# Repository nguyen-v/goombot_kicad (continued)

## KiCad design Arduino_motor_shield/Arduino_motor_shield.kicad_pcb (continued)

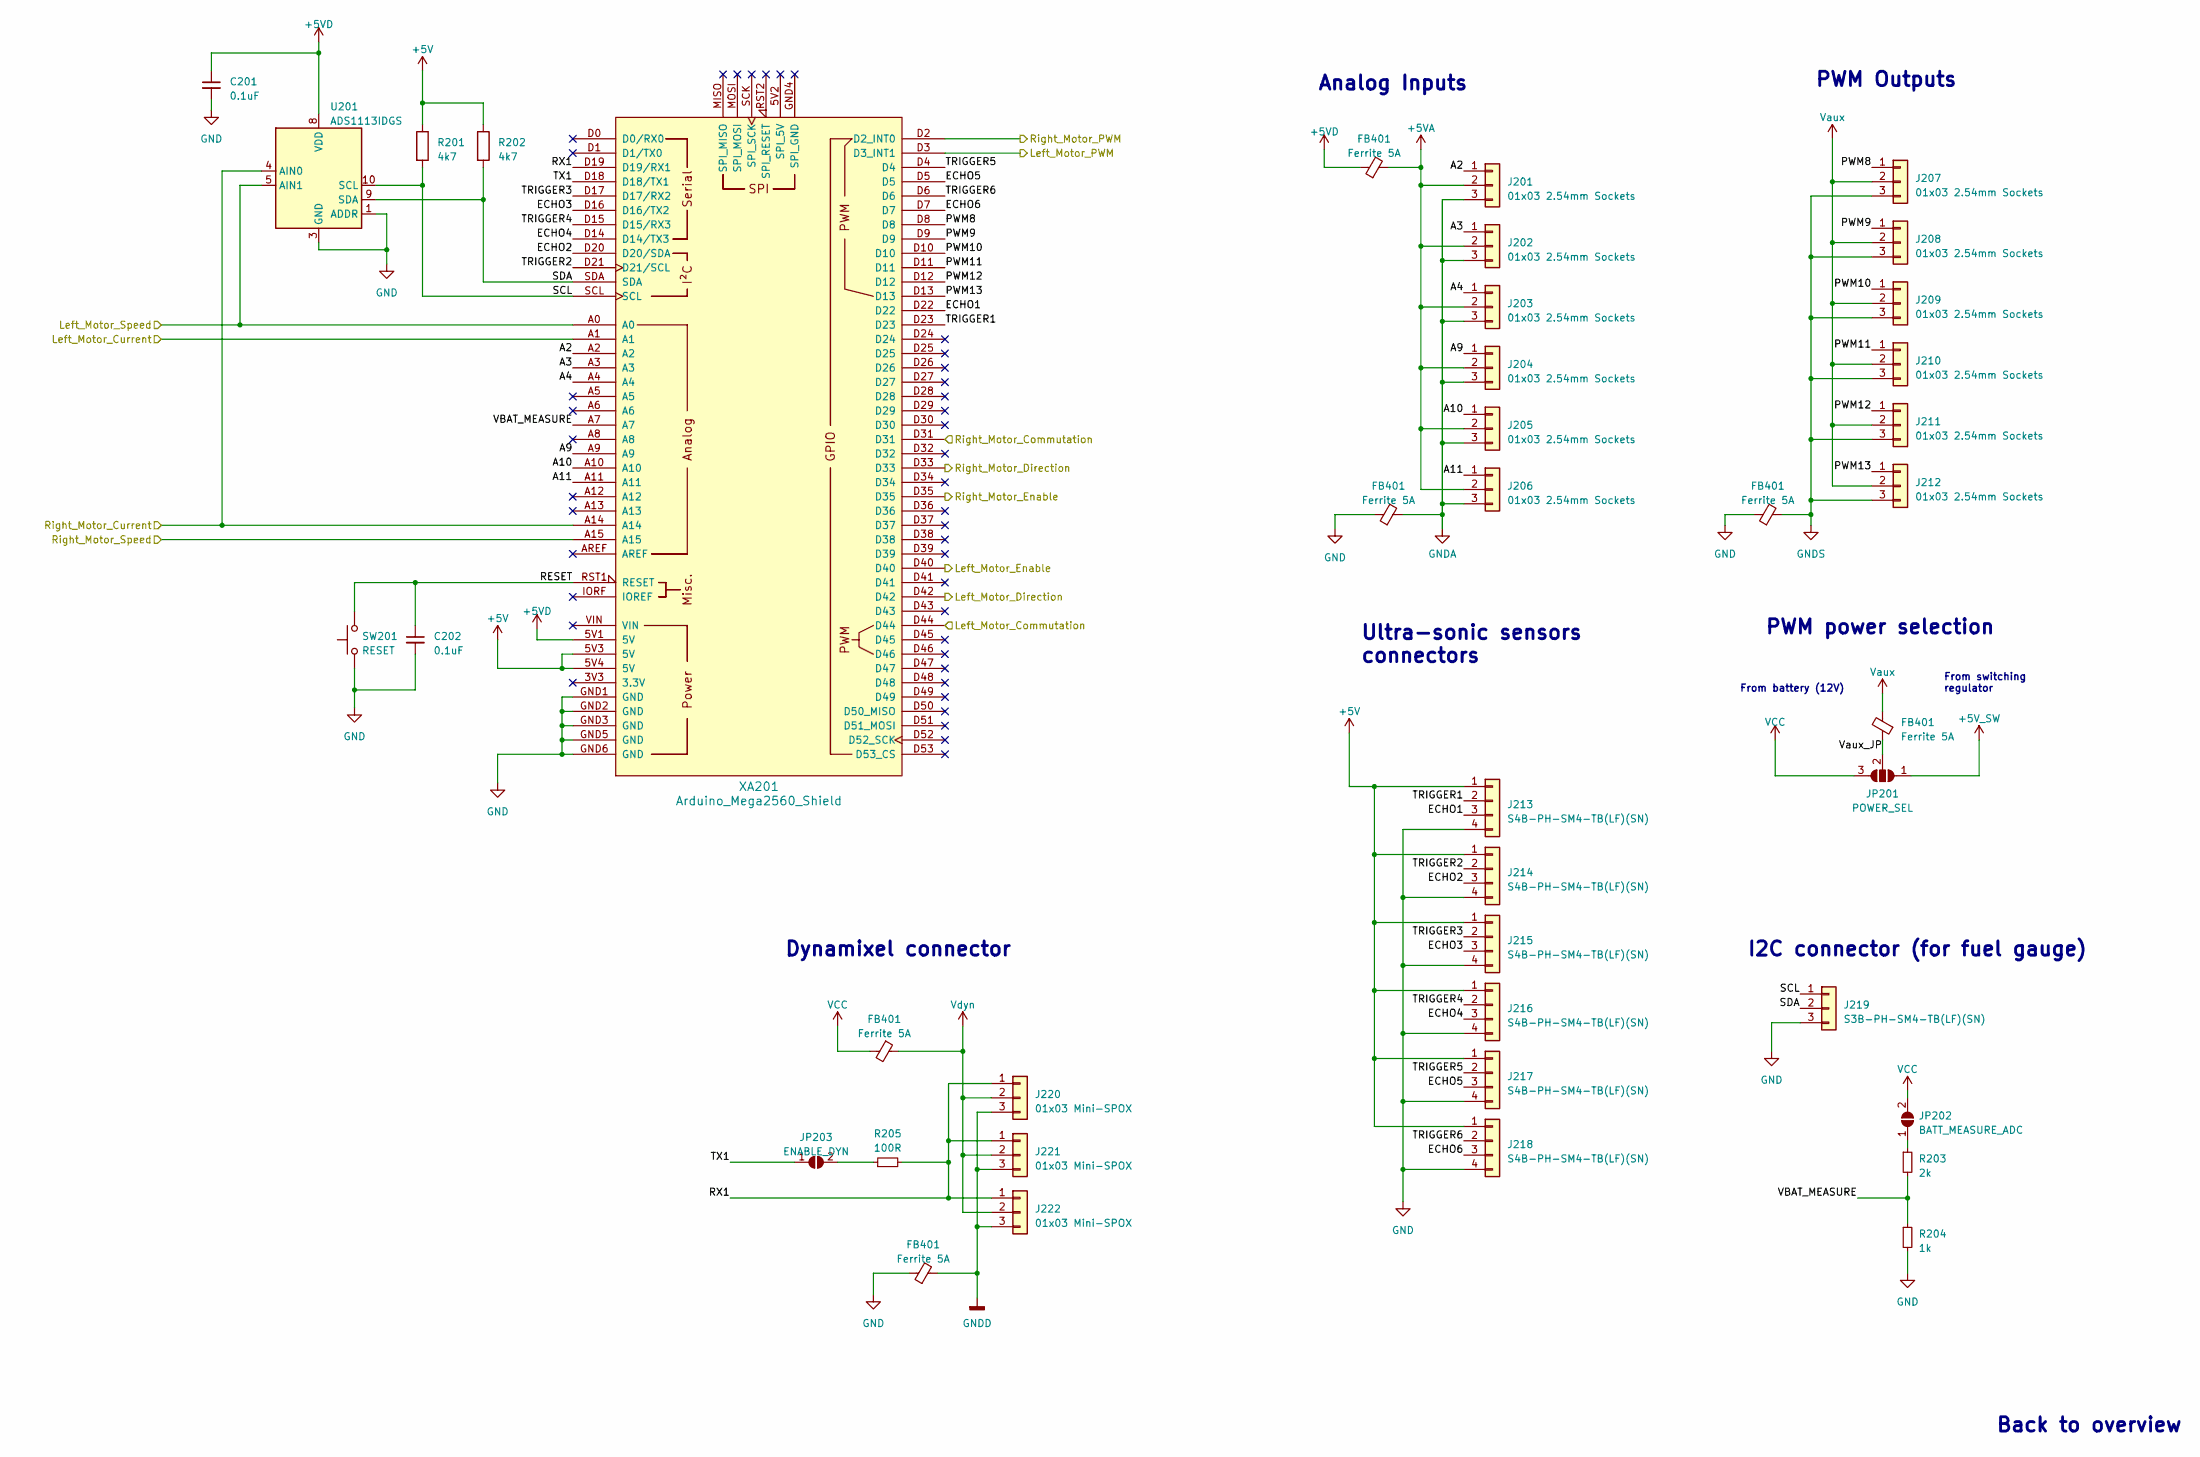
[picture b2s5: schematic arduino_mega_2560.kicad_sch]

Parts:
C201, C202: 0.1uF; C_0603_1608Metric
FB401: Ferrite 5A; L_0603_1608Metric
J201, J202, J203, J204, J205, J206, J207, J208, J209, J210, J211, J212: 01x03 2.54mm Sockets; PinSocket_1x03_P2.54mm_Vertical
J213, J214, J215, J216, J217, J218: S4B-PH-SM4-TB(LF)(SN); JST_PH_S4B-PH-SM4-TB_1x04-1MP_P2.00mm_Horizontal
J219: S3B-PH-SM4-TB(LF)(SN); JST_PH_S3B-PH-SM4-TB_1x03-1MP_P2.00mm_Horizontal
J220, J221, J222: 01x03 Mini-SPOX; MOLEX_0022057035_5268-03A
JP201: POWER_SEL; SolderJumper-3_P1.3mm_Open_RoundedPad1.0x1.5mm
JP202: BATT_MEASURE_ADC; SolderJumper-2_P1.3mm_Open_RoundedPad1.0x1.5mm
JP203: ENABLE_DYN; SolderJumper-2_P1.3mm_Open_RoundedPad1.0x1.5mm
R201, R202: 4k7; R_0603_1608Metric
R203: 2k; R_0603_1608Metric
R204: 1k; R_0603_1608Metric
R205: 100R; R_0603_1608Metric
SW201: RESET; MJTP1140ATR
U201: ADS1113IDGS; TSSOP-10_3x3mm_P0.5mm
XA201: Arduino_Mega2560_Shield

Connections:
+5V: J213.1, J214.1, J215.1, J216.1, J217.1, J218.1, R201.1, R202.1, XA201.5V3 (5V), XA201.5V4 (5V)
+5VA: J201.2, J202.2, J203.2, J204.2, J205.2, J206.2; also elsewhere on the board
+5VD: C201.1, U201.8 (VDD), XA201.5V1 (5V); also elsewhere on the board
/Arduino Mega 2560/A2: J201.1, XA201.A2
/Arduino Mega 2560/A3: J202.1, XA201.A3
/Arduino Mega 2560/A4: J203.1, XA201.A4
/Arduino Mega 2560/A9: J204.1, XA201.A9
/Arduino Mega 2560/A10: J205.1, XA201.A10
/Arduino Mega 2560/A11: J206.1, XA201.A11
/Arduino Mega 2560/ECHO1: J213.3, XA201.D22
/Arduino Mega 2560/ECHO2: J214.3, XA201.D20 (D20/SDA)
/Arduino Mega 2560/ECHO3: J215.3, XA201.D16 (D16/TX2)
/Arduino Mega 2560/ECHO4: J216.3, XA201.D14 (D14/TX3)
/Arduino Mega 2560/ECHO5: J217.3, XA201.D5
/Arduino Mega 2560/ECHO6: J218.3, XA201.D7
/Arduino Mega 2560/Left_Motor_Commutation: XA201.D44; also elsewhere on the board
/Arduino Mega 2560/Left_Motor_Current: XA201.A1; also elsewhere on the board
/Arduino Mega 2560/Left_Motor_Direction: XA201.D42; also elsewhere on the board
/Arduino Mega 2560/Left_Motor_Enable: XA201.D40; also elsewhere on the board
/Arduino Mega 2560/Left_Motor_PWM: XA201.D3 (D3_INT1); also elsewhere on the board
/Arduino Mega 2560/Left_Motor_Speed: U201.5 (AIN1), XA201.A0; also elsewhere on the board
/Arduino Mega 2560/PWM8: J207.1, XA201.D8
/Arduino Mega 2560/PWM9: J208.1, XA201.D9
/Arduino Mega 2560/PWM10: J209.1, XA201.D10
/Arduino Mega 2560/PWM11: J210.1, XA201.D11
/Arduino Mega 2560/PWM12: J211.1, XA201.D12
/Arduino Mega 2560/PWM13: J212.1, XA201.D13
/Arduino Mega 2560/RESET: C202.1, SW201.2, XA201.RST1 (RESET)
/Arduino Mega 2560/RX1: J220.1, J221.1, J222.1, R205.2, XA201.D19 (D19/RX1)
/Arduino Mega 2560/Right_Motor_Commutation: XA201.D31; also elsewhere on the board
/Arduino Mega 2560/Right_Motor_Current: U201.4 (AIN0), XA201.A14; also elsewhere on the board
/Arduino Mega 2560/Right_Motor_Direction: XA201.D33; also elsewhere on the board
/Arduino Mega 2560/Right_Motor_Enable: XA201.D35; also elsewhere on the board
/Arduino Mega 2560/Right_Motor_PWM: XA201.D2 (D2_INT0); also elsewhere on the board
/Arduino Mega 2560/Right_Motor_Speed: XA201.A15; also elsewhere on the board
/Arduino Mega 2560/SCL: J219.1, R201.2, U201.10 (SCL), XA201.SCL
/Arduino Mega 2560/SDA: J219.2, R202.2, U201.9 (SDA), XA201.SDA
/Arduino Mega 2560/TRIGGER1: J213.2, XA201.D23
/Arduino Mega 2560/TRIGGER2: J214.2, XA201.D21 (D21/SCL)
/Arduino Mega 2560/TRIGGER3: J215.2, XA201.D17 (D17/RX2)
/Arduino Mega 2560/TRIGGER4: J216.2, XA201.D15 (D15/RX3)
/Arduino Mega 2560/TRIGGER5: J217.2, XA201.D4
/Arduino Mega 2560/TRIGGER6: J218.2, XA201.D6
/Arduino Mega 2560/TX1: JP203.1 (A), XA201.D18 (D18/TX1)
/Arduino Mega 2560/Vaux_JP: JP201.2 (C); also elsewhere on the board
GNDA: J201.3, J202.3, J203.3, J204.3, J205.3, J206.3; also elsewhere on the board
GNDD: J220.3, J221.3, J222.3; also elsewhere on the board
GNDS: J207.3, J208.3, J209.3, J210.3, J211.3, J212.3; also elsewhere on the board
unnamed: JP202.1 (A), R203.1
unnamed: JP203.2 (B), R205.1
VCC: JP201.3 (B), JP202.2 (B); also elsewhere on the board
Vaux: J207.2, J208.2, J209.2, J210.2, J211.2, J212.2; also elsewhere on the board
Vdyn: J220.2, J221.2, J222.2; also elsewhere on the board

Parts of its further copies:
FB201, FB202, FB203, FB204, FB205, FB206: Ferrite 5A; L_0603_1608Metric

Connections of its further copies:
+5VA: FB202.2; also elsewhere on the board
+5VD: FB202.1; also elsewhere on the board
/Arduino Mega 2560/Vaux_JP: FB204.1; also elsewhere on the board
GNDA: FB201.2; also elsewhere on the board
GNDD: FB206.2; also elsewhere on the board
GNDS: FB203.2; also elsewhere on the board
VCC: FB205.2; also elsewhere on the board
Vaux: FB204.2; also elsewhere on the board
Vdyn: FB205.1; also elsewhere on the board

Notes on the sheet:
From switching regulator
From battery (12V)
PWM Outputs
Analog Inputs
Dynamixel connector
I2C connector (for fuel gauge)
PWM power selection
Back to overview
Ultra-sonic sensors connectors

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
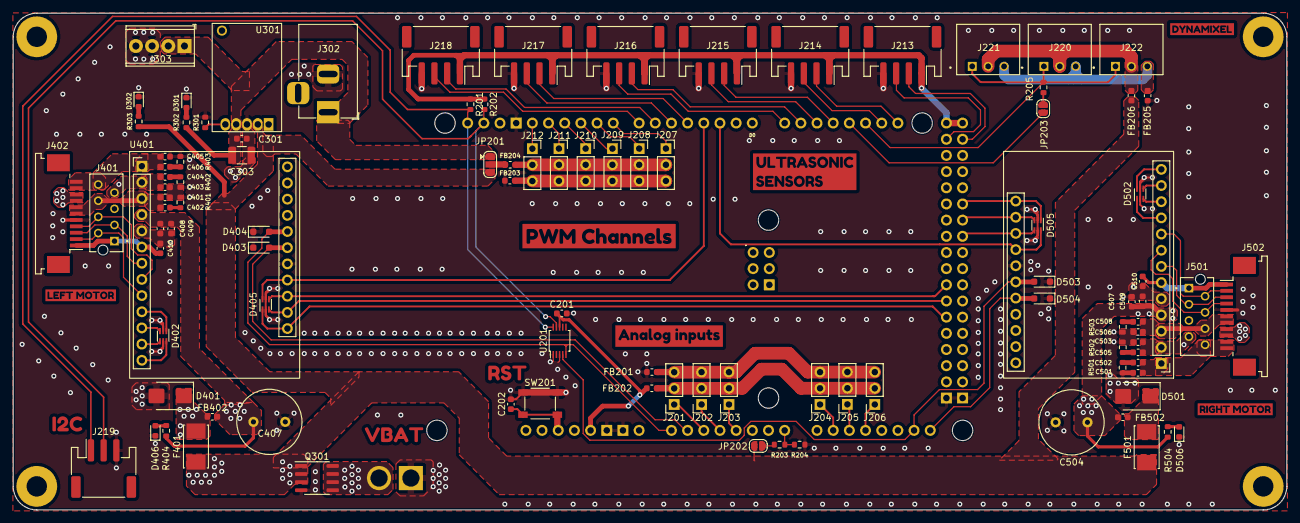
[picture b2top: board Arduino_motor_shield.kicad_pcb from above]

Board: 2 copper layers, 200.0 x 78.0 mm, 149 parts (1 on the bottom side), 94 nets.

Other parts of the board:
kibuzzard-6436BD05: G***; kibuzzard-6436BD05
kibuzzard-6436BD85: G***; kibuzzard-6436BD85
kibuzzard-6436BDA4: G***; kibuzzard-6436BDA4
kibuzzard-6436BDB6: G***; kibuzzard-6436BDB6
kibuzzard-6436BE0F: G***; kibuzzard-6436BE0F
kibuzzard-6436BE25: G***; kibuzzard-6436BE25
kibuzzard-6436BE36: G***; kibuzzard-6436BE36
kibuzzard-6436BEC4: G***; kibuzzard-6436BEC4
kibuzzard-6436BECD: G***; kibuzzard-6436BECD
kibuzzard-6436BED4: G***; kibuzzard-6436BED4
kibuzzard-6436BEDB: G***; kibuzzard-6436BEDB
kibuzzard-6436BEE8: G***; kibuzzard-6436BEE8
kibuzzard-6436BEF0: G***; kibuzzard-6436BEF0
kibuzzard-6436BF7A, kibuzzard-6436BF7A#2: G***; kibuzzard-6436BF7A
kibuzzard-6436BF9D, kibuzzard-6436BF9D#2, kibuzzard-6436BF9D#3, kibuzzard-6436BF9D#4: G***; kibuzzard-6436BF9D
kibuzzard-6436BF49: G***; kibuzzard-6436BF49
kibuzzard-6436BFC3: G***; kibuzzard-6436BFC3
kibuzzard-6436C0DF: G***; kibuzzard-6436C0DF
kibuzzard-6436C002: G***; kibuzzard-6436C002
kibuzzard-6436C2A5: G***; kibuzzard-6436C2A5
kibuzzard-6436C2D2: G***; kibuzzard-6436C2D2
kibuzzard-6436C3BB: G***; kibuzzard-6436C3BB
kibuzzard-6436C3CE: G***; kibuzzard-6436C3CE
kibuzzard-6436C4A8: G***; kibuzzard-6436C4A8
kibuzzard-6436C4AB: G***; kibuzzard-6436C4AB
kibuzzard-6436C4B8: G***; kibuzzard-6436C4B8
kibuzzard-6436C4F6: G***; kibuzzard-6436C4F6
kibuzzard-6436C26E: G***; kibuzzard-6436C26E
kibuzzard-6436C28D: G***; kibuzzard-6436C28D
kibuzzard-6436C31D, kibuzzard-6436C31D#2: G***; kibuzzard-6436C31D
kibuzzard-6436C50F: G***; kibuzzard-6436C50F
kibuzzard-6436C52E: G***; kibuzzard-6436C52E
kibuzzard-6436C224: G***; kibuzzard-6436C224
kibuzzard-6436C547: G***; kibuzzard-6436C547
kibuzzard-6436C551: G***; kibuzzard-6436C551
kibuzzard-6436C957: G***; kibuzzard-6436C957
kibuzzard-6436CBBB: G***; kibuzzard-6436CBBB

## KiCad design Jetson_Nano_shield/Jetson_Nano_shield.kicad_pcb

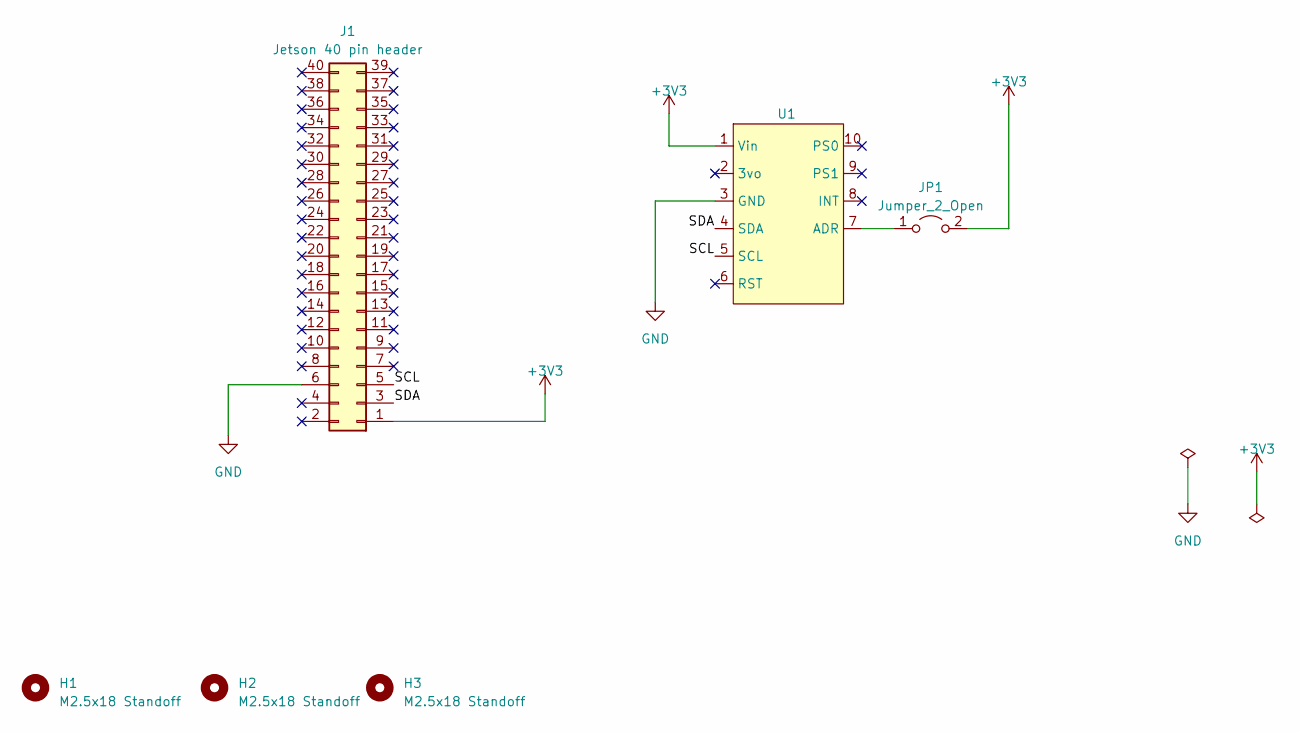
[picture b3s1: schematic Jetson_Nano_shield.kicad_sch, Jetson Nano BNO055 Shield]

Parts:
H1, H2, H3: M2.5x18 Standoff; MountingHole_2.7mm_Pad
J1: Jetson 40 pin header; 2x20 stacking headers
JP1: Jumper_2_Open; SolderJumper-2_P1.3mm_Open_RoundedPad1.0x1.5mm
U1: BNO055

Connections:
+3V3: J1.1, JP1.2 (B), U1.1 (Vin)
/SCL: J1.5, U1.5 (SCL)
/SDA: J1.3, U1.4 (SDA)
GND: J1.6, U1.3 (GND)
unnamed: JP1.1 (A), U1.7 (ADR)

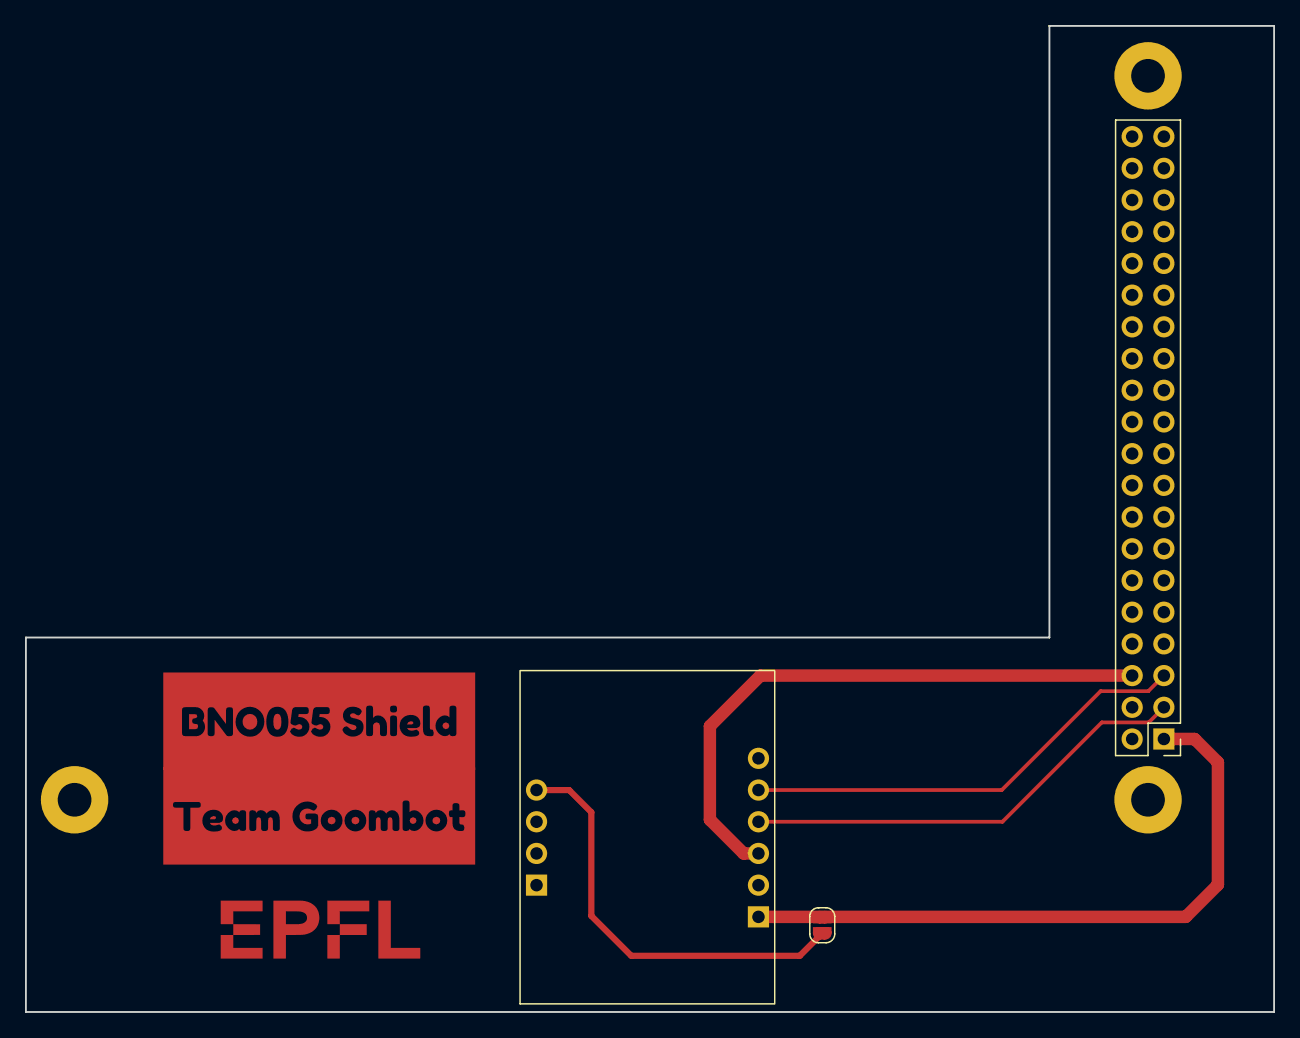
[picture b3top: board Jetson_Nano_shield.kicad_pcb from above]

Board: 2 copper layers, 100.0 x 79.0 mm, 8 parts (0 on the bottom side), 5 nets.

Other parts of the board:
kibuzzard-6431C73E: G***; kibuzzard-6431C73E
kibuzzard-6431C739: G***; kibuzzard-6431C739

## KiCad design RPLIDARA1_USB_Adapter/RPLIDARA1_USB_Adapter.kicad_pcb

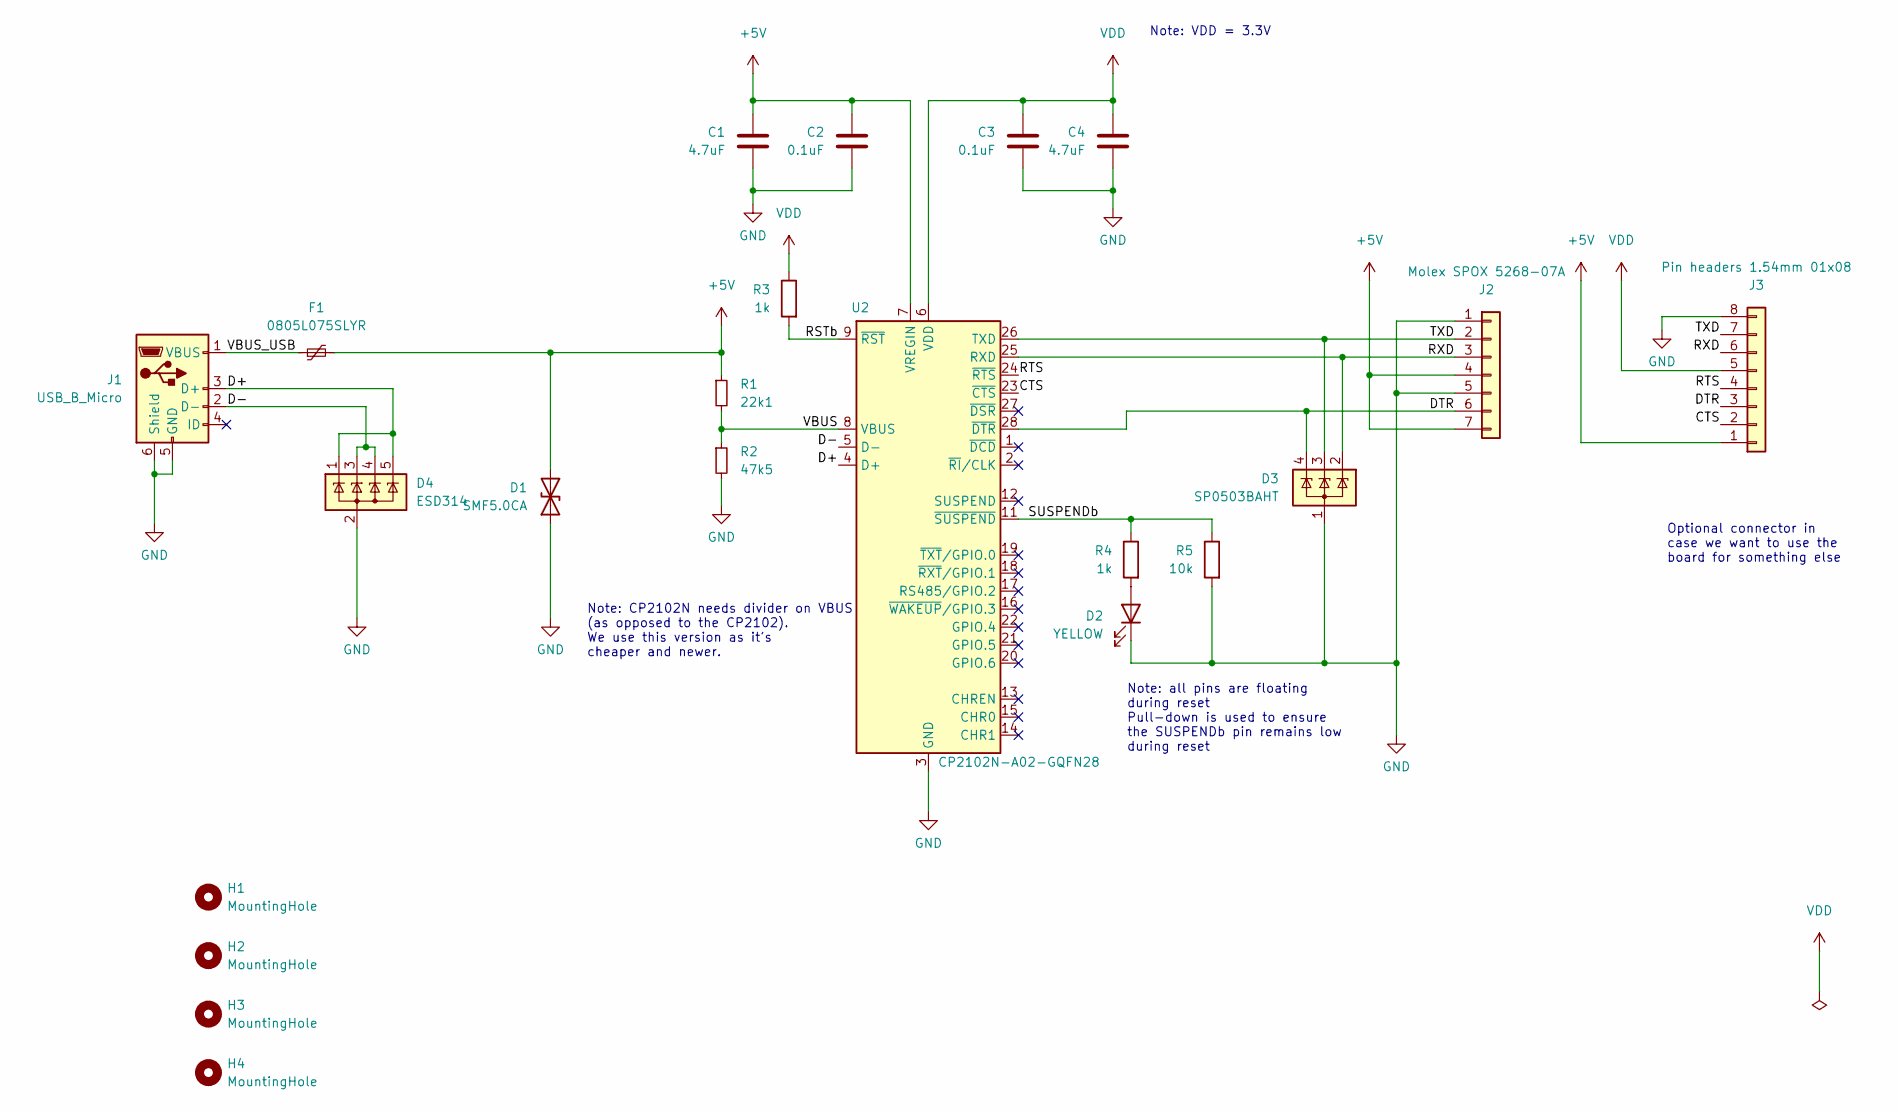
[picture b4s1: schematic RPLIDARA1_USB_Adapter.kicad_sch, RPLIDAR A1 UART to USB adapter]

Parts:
C1, C4: 4.7uF; C_0603_1608Metric
C2, C3: 0.1uF; C_0603_1608Metric
D1: SMF5.0CA; D_SOD-123
D2: YELLOW; LED_0603_1608Metric
D3: SP0503BAHT; SOT-143
D4: ESD314; SOT-23-5
F1: 0805L075SLYR; Fuse_0805_2012Metric; Digikey ref F4151CT-ND
H1, H2, H3, H4: MountingHole; MountingHole_2.2mm_M2
J1: USB_B_Micro; USB_Micro-B_Molex-105017-0001
J2: Molex SPOX 5268-07A; Molex_SPOX_5268-07A_1x07_P2.50mm_Horizontal
J3: Pin headers 1.54mm 01x08; PinHeader_1x08_P2.54mm_Vertical
R1: 22k1; R_0603_1608Metric
R2: 47k5; R_0603_1608Metric
R3, R4: 1k; R_0603_1608Metric
R5: 10k; R_0603_1608Metric
U2: CP2102N-A02-GQFN28; QFN-28-1EP_5x5mm_P0.5mm_EP3.35x3.35mm

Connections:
+5V: C1.1, C2.1, D1.2 (A2), F1.2, J2.4, J2.7, J3.1, R1.1, U2.7 (VREGIN)
/CTS: J3.2, U2.23 (~CTS)
/D+: D4.1 (I/O1), D4.5 (I/O4), J1.3 (D+), U2.4 (D+)
/D-: D4.3 (I/O2), D4.4 (I/O3), J1.2 (D-), U2.5 (D-)
/DTR: D3.4 (K), J2.6, J3.3, U2.28 (~DTR)
/RSTb: R3.2, U2.9 (~RST)
/RTS: J3.4, U2.24 (~RTS)
/RXD: D3.2 (K), J2.3, J3.6, U2.25 (RXD)
/SUSPENDb: R4.1, R5.1, U2.11 (~SUSPEND)
/TXD: D3.3 (K), J2.2, J3.7, U2.26 (TXD)
/VBUS: R1.2, R2.1, U2.8 (VBUS)
/VBUS_USB: F1.1, J1.1 (VBUS)
GND: C1.2, C2.2, C3.2, C4.2, D1.1 (A1), D2.1 (K), D3.1 (A), D4.2 (GND), J1.5 (GND), J1.6 (Shield), J2.1, J2.5, J3.8, R2.2, R5.2, U2.3 (GND), U2.29 (GND)
unnamed: D2.2 (A), R4.2
VDD: C3.1, C4.1, J3.5, R3.1, U2.6 (VDD)

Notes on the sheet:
Note: CP2102N needs divider on VBUS (as opposed to the CP2102). We use this version as it's cheaper and newer.
Optional connector in case we want to use the board for something else
Note: all pins are floating during reset Pull-down is used to ensure the SUSPENDb pin remains low during reset
Note: VDD = 3.3V

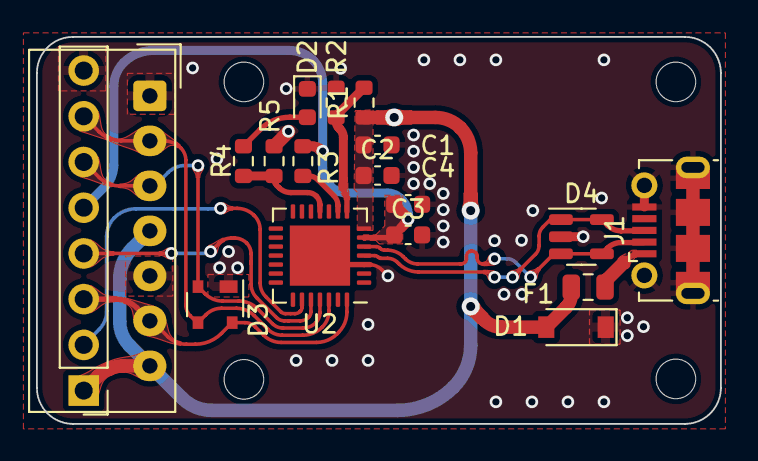
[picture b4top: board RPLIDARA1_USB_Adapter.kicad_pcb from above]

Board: 2 copper layers, 38.0 x 21.5 mm, 24 parts (1 on the bottom side), 15 nets.

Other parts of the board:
kibuzzard-6407C140: G***; kibuzzard-6407C140
kibuzzard-6407C165: G***; kibuzzard-6407C165

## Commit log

2023-03-07 added base files for usb adapter
2023-03-07 Added RPLIDAR A1 USB Adapter board
2023-03-07 Modified texts
2023-03-07 moved pin 1 indicator
2023-04-12 added jetson IMU shield and Arduino mega motor shield
2023-04-12 added step file for arduino motor shield
2023-04-18 Added PCB for LiPo protection board
2023-04-18 Added BOM to LiPo board
2023-04-18 updated html bom (lipo)
2023-04-18 added via in pad for fuse for anti-shear
